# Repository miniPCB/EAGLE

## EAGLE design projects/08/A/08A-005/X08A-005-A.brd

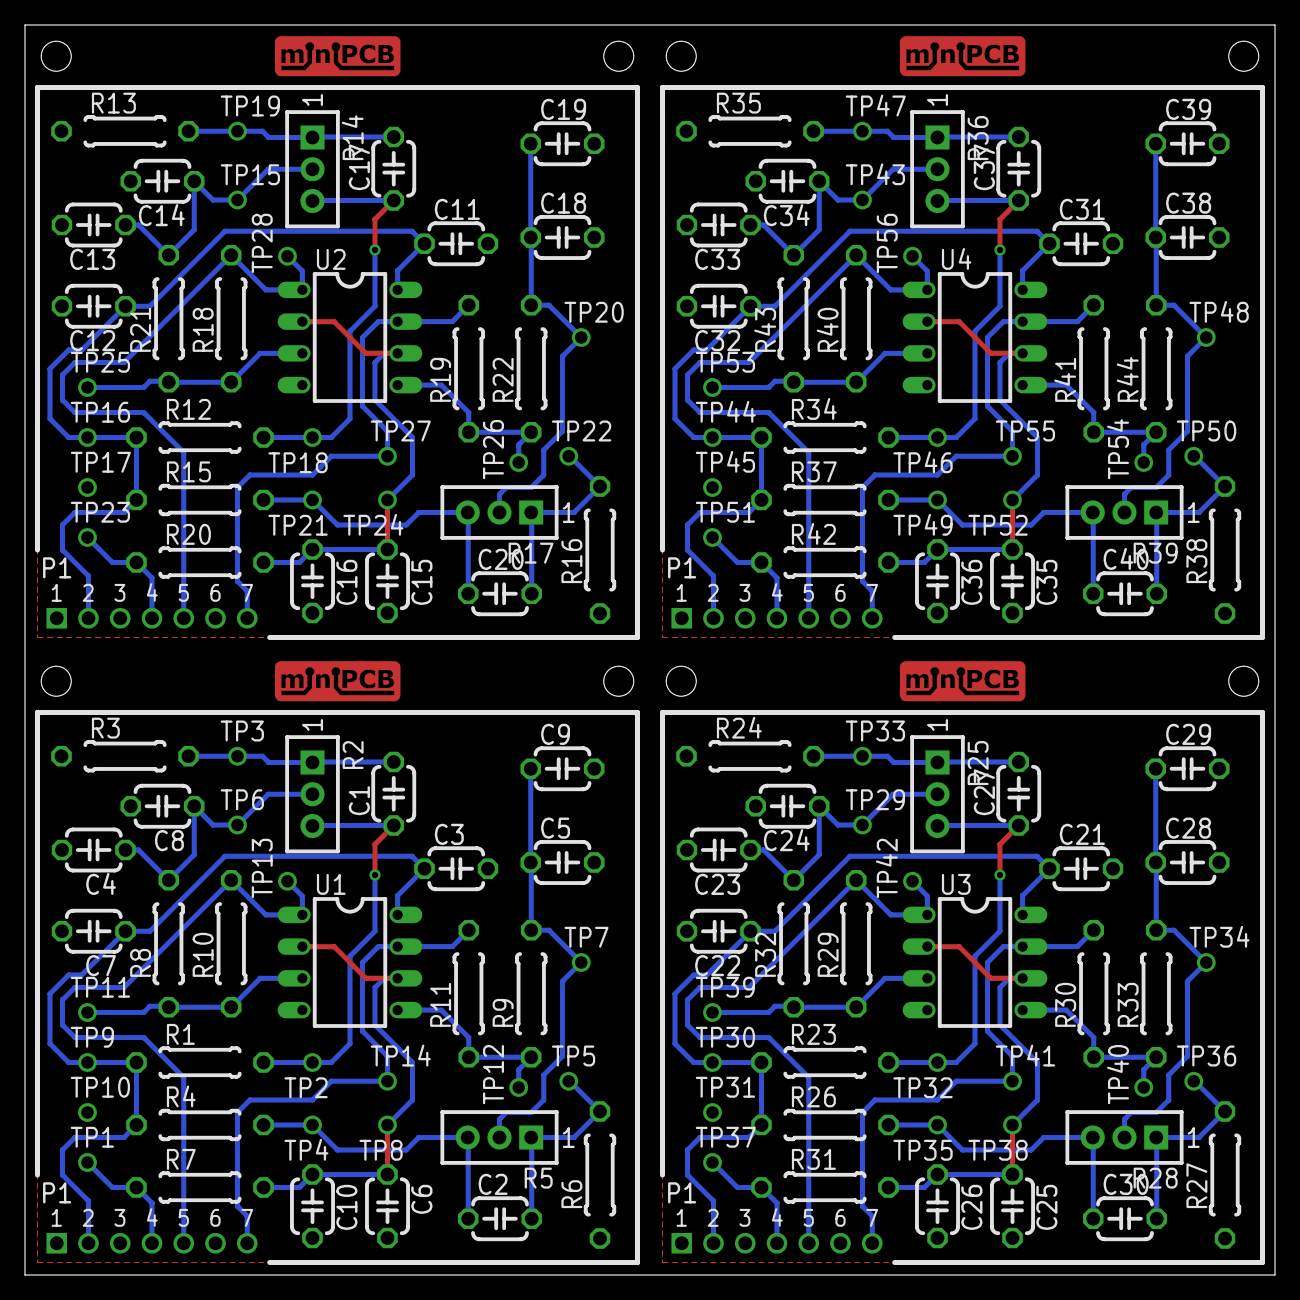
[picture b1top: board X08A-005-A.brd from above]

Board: 2 copper layers, 100.0 x 100.0 mm, 149 parts (0 on the bottom side), 56 nets.

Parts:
C1, C2, C3, C4, C5, C6, C7, C8, C9, C10, C11, C12, C13, C14, C15, C16, C17, C18, C19, C20, C21, C22, C23, C24, C25, C26, C27, C28, C29, C30, C31, C32, C33, C34, C35, C36, C37, C38, C39, C40: C050-024X044
E$1: MINIPCB_PANEL_IMAGEFRAME
P1-, P1-1, P1-2, P1-3: MINIPCB_7P_50X50
R1, R3, R4, R6, R7, R8, R9, R10, R11, R12, R13, R15, R16, R18, R19, R20, R21, R22, R23, R24, R26, R27, R29, R30, R31, R32, R33, R34, R35, R37, R38, R40, R41, R42, R43, R44: 0207/10
R2, R5, R14, R17, R25, R28, R36, R39: TRIM_0100
TP1, TP2, TP3, TP4, TP5, TP6, TP7, TP8, TP9, TP10, TP11, TP12, TP13, TP14, TP15, TP16, TP17, TP18, TP19, TP20, TP21, TP22, TP23, TP24, TP25, TP26, TP27, TP28, TP29, TP30, TP31, TP32, TP33, TP34, TP35, TP36, TP37, TP38, TP39, TP40, TP41, TP42, TP43, TP44, TP45, TP46, TP47, TP48, TP49, TP50, TP51, TP52, TP53, TP54, TP55, TP56: PINS_1_TESTPOINT_KE5000_NOTEXT
U1, U2, U3, U4: DIL08

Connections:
BIASA: C4.1, C8.1, R2.2, R8.2, TP6.1
BIASA1: C13.1, C14.1, R14.2, R21.2, TP15.1
BIASA2: C23.1, C24.1, R25.2, R32.2, TP29.1
BIASA3: C33.1, C34.1, R36.2, R43.2, TP43.1
BIASB: C5.1, C9.1, R5.2, R9.2, TP7.1
BIASB1: C18.1, C19.1, R17.2, R22.2, TP20.1
BIASB2: C28.1, C29.1, R28.2, R33.2, TP34.1
BIASB3: C38.1, C39.1, R39.2, R44.2, TP48.1
GND: C3.2, C4.2, C5.2, C6.2, C7.2, C8.2, C9.2, C10.2, P1-.1, R3.1, R6.1, TP10.1, U1.4
GND1: C11.2, C12.2, C13.2, C14.2, C15.2, C16.2, C18.2, C19.2, P1-1.1, R13.1, R16.1, TP17.1, U2.4
GND2: C21.2, C22.2, C23.2, C24.2, C25.2, C26.2, C28.2, C29.2, P1-2.1, R24.1, R27.1, TP31.1, U3.4
GND3: C31.2, C32.2, C33.2, C34.2, C35.2, C36.2, C38.2, C39.2, P1-3.1, R35.1, R38.1, TP45.1, U4.4
IN: P1-.4, R7.1, TP1.1
IN1: P1-1.4, R20.1, TP23.1
IN2: P1-2.4, R31.1, TP37.1
IN3: P1-3.4, R42.1, TP51.1
IN-4: C6.1, C10.1, R7.2, TP8.1, U1.2, U1.6
IN-5: C15.1, C16.1, R20.2, TP24.1, U2.2, U2.6
IN-6: C25.1, C26.1, R31.2, TP38.1, U3.2, U3.6
IN-7: C35.1, C36.1, R42.2, TP52.1, U4.2, U4.6
INA+: R8.1, R10.1, TP11.1, U1.3
INA+1: R18.1, R21.1, TP25.1, U2.3
INA+2: R29.1, R32.1, TP39.1, U3.3
INA+3: R40.1, R43.1, TP53.1, U4.3
INB+: R9.1, R11.1, TP12.1, U1.5
INB+1: R19.1, R22.1, TP26.1, U2.5
INB+2: R30.1, R33.1, TP40.1, U3.5
INB+3: R41.1, R44.1, TP54.1, U4.5
OUTA: P1-.5, R10.2, TP13.1, U1.1
OUTA1: P1-1.5, R18.2, TP28.1, U2.1
OUTA2: P1-2.5, R29.2, TP42.1, U3.1
OUTA3: P1-3.5, R40.2, TP56.1, U4.1
OUTB: P1-.7, R11.2, TP14.1, U1.7
OUTB1: P1-1.7, R19.2, TP27.1, U2.7
OUTB2: P1-2.7, R30.2, TP41.1, U3.7
OUTB3: P1-3.7, R41.2, TP55.1, U4.7
R2.1: C1.1, R1.2, R2.3, TP2.1
R2.4: C1.2, R2.1, R3.2, TP3.1
R2.6: C17.1, R12.2, R14.3, TP18.1
R2.8: C17.2, R13.2, R14.1, TP19.1
R2.9: C27.1, R23.2, R25.3, TP32.1
R2.10: C27.2, R24.2, R25.1, TP33.1
R2.11: C37.1, R34.2, R36.3, TP46.1
R2.12: C37.2, R35.2, R36.1, TP47.1
R5.1: C2.2, R5.1, R6.2, TP5.1
R5.2: C20.1, R15.2, R17.3, TP21.1
R5.3: C2.1, R4.2, R5.3, TP4.1
R5.4: C20.2, R16.2, R17.1, TP22.1
R5.5: C30.1, R26.2, R28.3, TP35.1
R5.6: C30.2, R27.2, R28.1, TP36.1
R5.7: C40.1, R37.2, R39.3, TP49.1
R5.8: C40.2, R38.2, R39.1, TP50.1
V+: C3.1, C7.1, P1-.2, R1.1, R4.1, TP9.1, U1.8
V+1: C11.1, C12.1, P1-1.2, R12.1, R15.1, TP16.1, U2.8
V+2: C21.1, C22.1, P1-2.2, R23.1, R26.1, TP30.1, U3.8
V+3: C31.1, C32.1, P1-3.2, R34.1, R37.1, TP44.1, U4.8

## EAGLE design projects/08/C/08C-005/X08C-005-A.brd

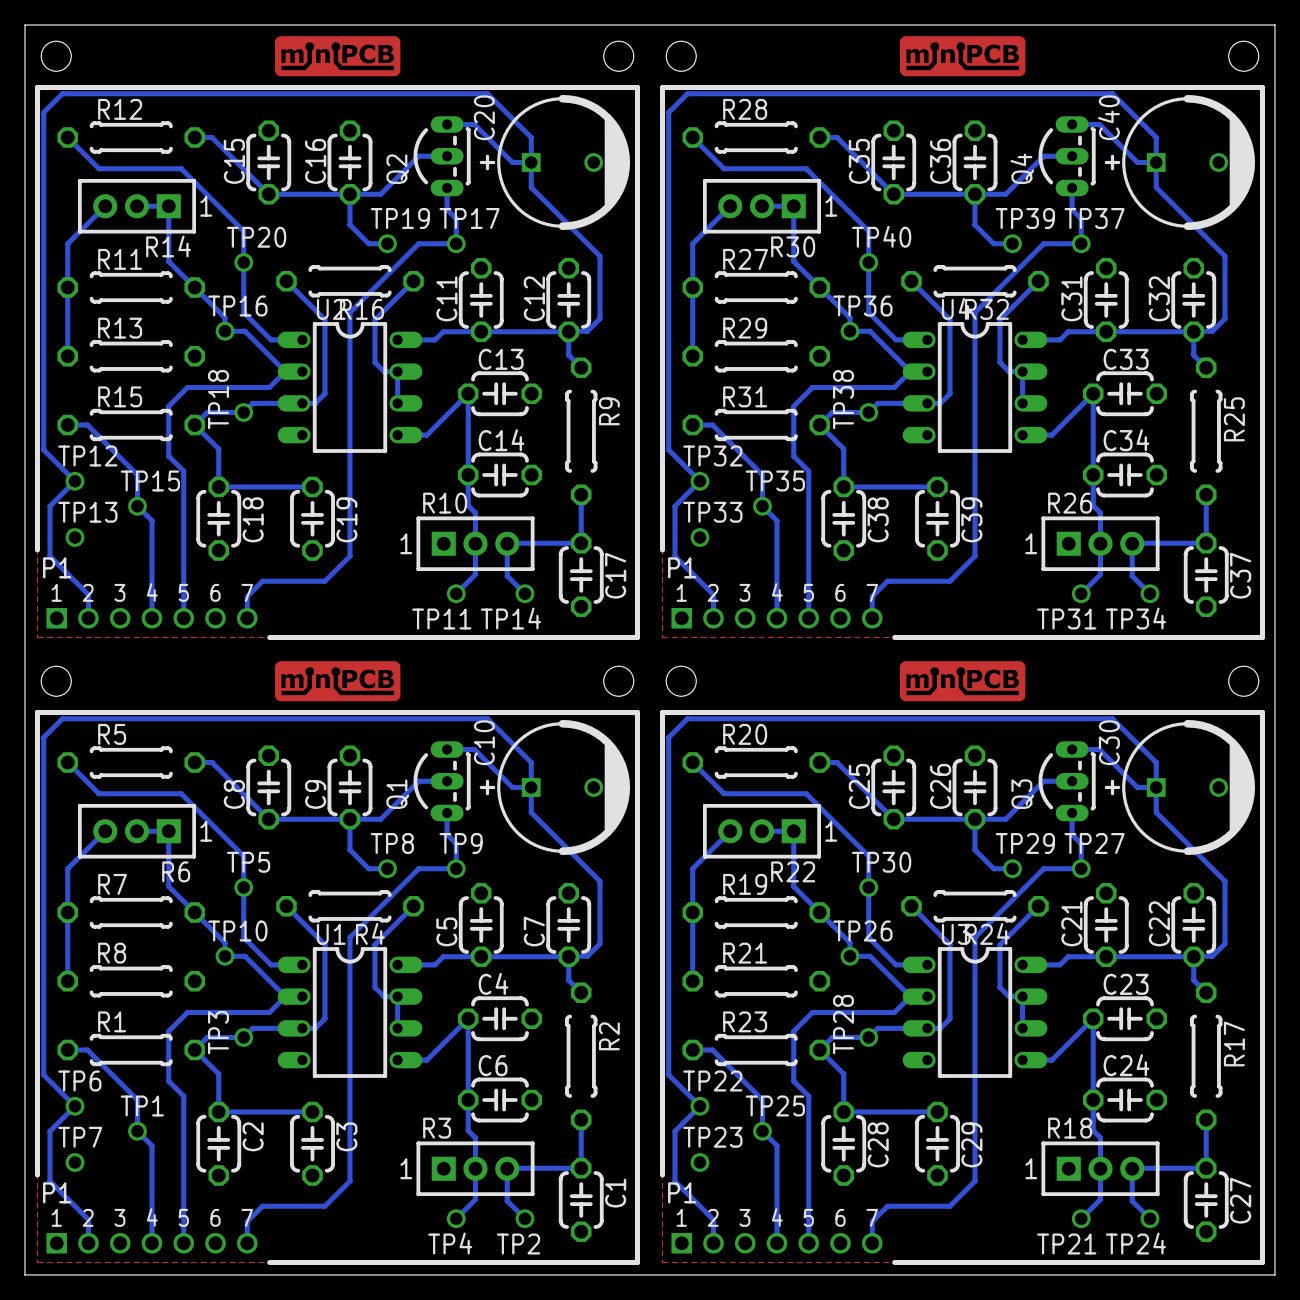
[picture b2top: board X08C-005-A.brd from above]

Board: 2 copper layers, 100.0 x 100.0 mm, 125 parts (0 on the bottom side), 48 nets.

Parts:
C1, C2, C3, C4, C5, C6, C7, C8, C9, C11, C12, C13, C14, C15, C16, C17, C18, C19, C21, C22, C23, C24, C25, C26, C27, C28, C29, C31, C32, C33, C34, C35, C36, C37, C38, C39: C050-024X044
C10, C20, C30, C40: C5MM
E$1: MINIPCB_PANEL_IMAGEFRAME
P1-, P1-1, P1-2, P1-3: MINIPCB_7P_50X50
Q1, Q2, Q3, Q4: TO92-EBC-OVAL
R1, R2, R4, R5, R7, R8, R9, R11, R12, R13, R15, R16, R17, R19, R20, R21, R23, R24, R25, R27, R28, R29, R31, R32: 0207/10
R3, R6, R10, R14, R18, R22, R26, R30: TRIM_0100
TP1, TP2, TP3, TP4, TP5, TP6, TP7, TP8, TP9, TP10, TP11, TP12, TP13, TP14, TP15, TP16, TP17, TP18, TP19, TP20, TP21, TP22, TP23, TP24, TP25, TP26, TP27, TP28, TP29, TP30, TP31, TP32, TP33, TP34, TP35, TP36, TP37, TP38, TP39, TP40: PINS_1_TESTPOINT_KE5000_NOTEXT
U1, U2, U3, U4: DIL08

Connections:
BIAS: C4.1, C6.1, R3.2, TP4.1, U1.5
BIAS1: C13.1, C14.1, R10.2, TP11.1, U2.5
BIAS2: C23.1, C24.1, R18.2, TP21.1, U3.5
BIAS3: C33.1, C34.1, R26.2, TP31.1, U4.5
GND: C1.2, C2.2, C3.2, C4.2, C5.2, C6.2, C7.2, C8.2, C9.2, C10.-, P1-.1, P1-.6, R3.1, R8.2, TP7.1, U1.4
GND1: C11.2, C12.2, C13.2, C14.2, C15.2, C16.2, C17.2, C18.2, C19.2, C20.-, P1-1.1, P1-1.6, R10.1, R13.2, TP13.1, U2.4
GND2: C21.2, C22.2, C23.2, C24.2, C25.2, C26.2, C27.2, C28.2, C29.2, C30.-, P1-2.1, P1-2.6, R18.1, R21.2, TP23.1, U3.4
GND3: C31.2, C32.2, C33.2, C34.2, C35.2, C36.2, C37.2, C38.2, C39.2, C40.-, P1-3.1, P1-3.6, R26.1, R29.2, TP33.1, U4.4
IN: R4.1, U1.6, U1.7
IN1: R16.1, U2.6, U2.7
IN2: R24.1, U3.6, U3.7
IN3: R32.1, U4.6, U4.7
unnamed: C2.1, C3.1, R1.2, R4.2, TP3.1, U1.3
unnamed: P1-.4, R1.1, TP1.1
unnamed: P1-1.4, R15.1, TP15.1
unnamed: C18.1, C19.1, R15.2, R16.2, TP18.1, U2.3
unnamed: P1-2.4, R23.1, TP25.1
unnamed: C28.1, C29.1, R23.2, R24.2, TP28.1, U3.3
unnamed: P1-3.4, R31.1, TP35.1
unnamed: C38.1, C39.1, R31.2, R32.2, TP38.1, U4.3
OUT+: P1-.7, Q1.E, TP9.1
OUT+1: P1-1.7, Q2.E, TP17.1
OUT+2: P1-2.7, Q3.E, TP27.1
OUT+3: P1-3.7, Q4.E, TP37.1
OUT-: P1-.5, R6.1, R6.2, R7.2, TP10.1, U1.2
OUT-1: P1-1.5, R11.2, R14.1, R14.2, TP16.1, U2.2
OUT-2: P1-2.5, R19.2, R22.1, R22.2, TP26.1, U3.2
OUT-3: P1-3.5, R27.2, R30.1, R30.2, TP36.1, U4.2
Q1.B: C8.1, C9.1, Q1.B, R5.2, TP8.1
Q1.B1: C15.1, C16.1, Q2.B, R12.2, TP19.1
Q1.B2: C25.1, C26.1, Q3.B, R20.2, TP29.1
Q1.B3: C35.1, C36.1, Q4.B, R28.2, TP39.1
R2.1: C17.1, R9.2, R10.3, TP14.1
R2.2: C27.1, R17.2, R18.3, TP24.1
R2.3: C1.1, R2.2, R3.3, TP2.1
R2.4: C37.1, R25.2, R26.3, TP34.1
R6.1: R11.1, R13.1, R14.3
R6.2: R19.1, R21.1, R22.3
R6.3: R6.3, R7.1, R8.1
R6.4: R27.1, R29.1, R30.3
U1.1: R5.1, TP5.1, U1.1
U1.2: R12.1, TP20.1, U2.1
U1.3: R20.1, TP30.1, U3.1
U1.4: R28.1, TP40.1, U4.1
V+: C5.1, C7.1, C10.+, P1-.2, Q1.C, R2.1, TP6.1, U1.8
V+1: C11.1, C12.1, C20.+, P1-1.2, Q2.C, R9.1, TP12.1, U2.8
V+2: C21.1, C22.1, C30.+, P1-2.2, Q3.C, R17.1, TP22.1, U3.8
V+3: C31.1, C32.1, C40.+, P1-3.2, Q4.C, R25.1, TP32.1, U4.8

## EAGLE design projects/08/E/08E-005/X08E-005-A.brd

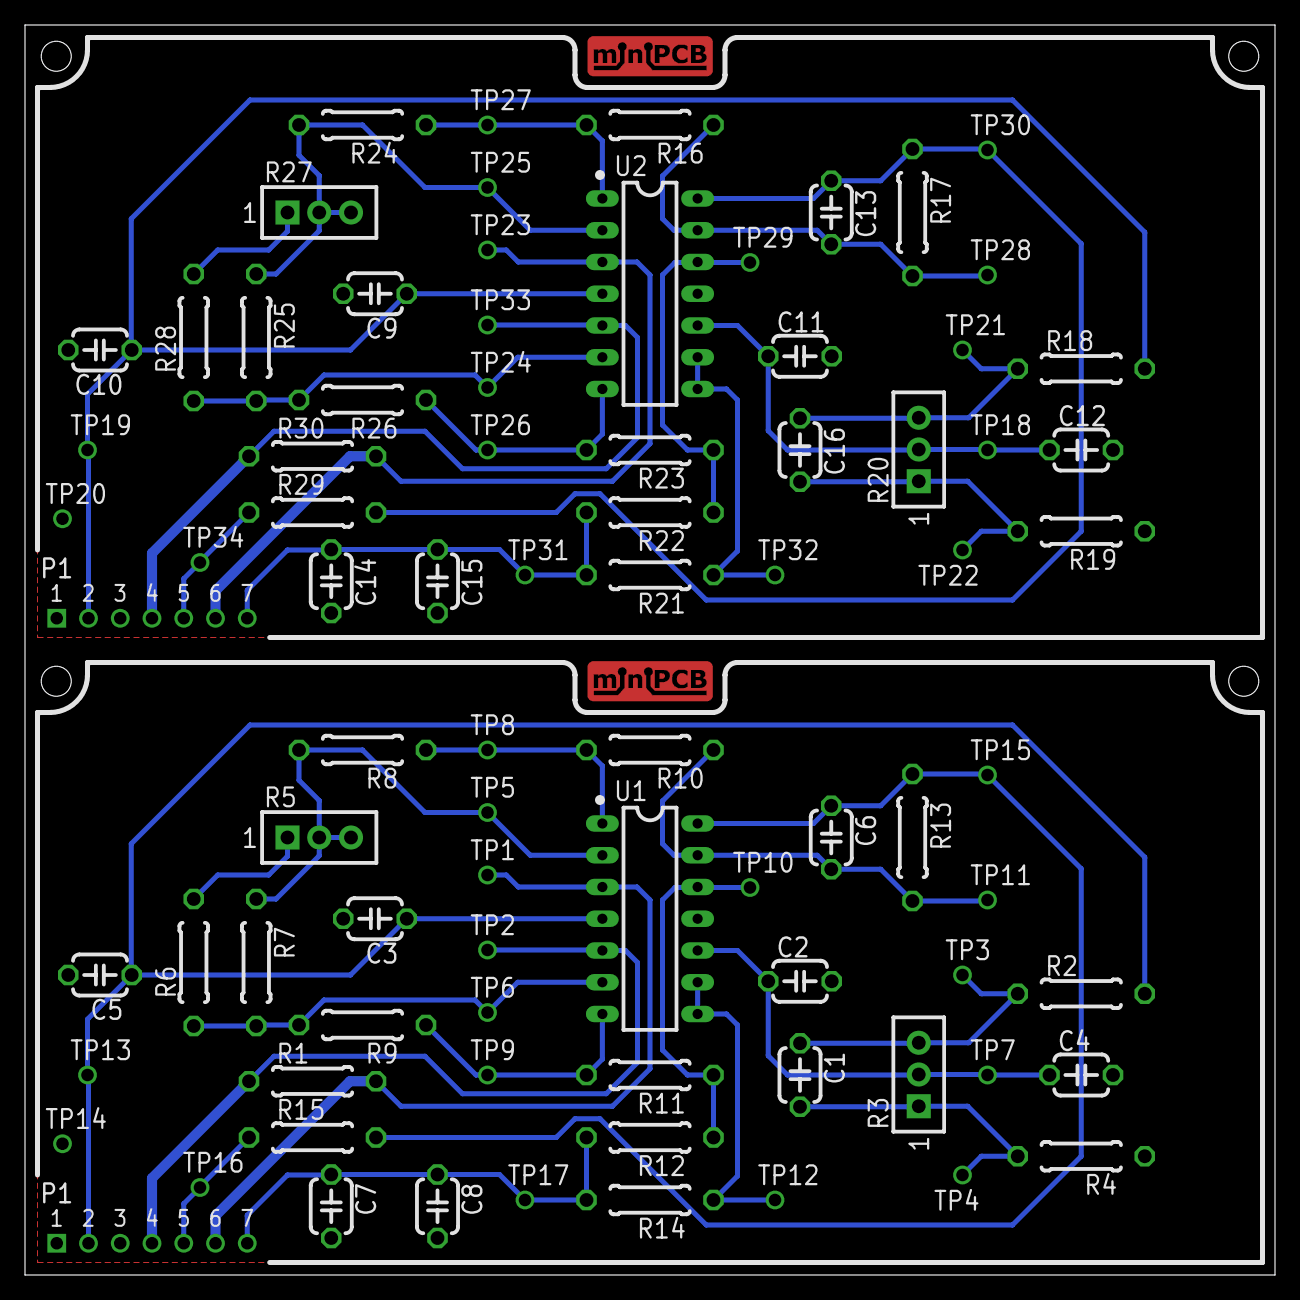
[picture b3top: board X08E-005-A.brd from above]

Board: 2 copper layers, 100.0 x 100.0 mm, 85 parts (0 on the bottom side), 36 nets.

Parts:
C1, C2, C3, C4, C5, C6, C7, C8, C9, C10, C11, C12, C13, C14, C15, C16: C050-024X044
E$1: MINIPCB_PANEL_IMAGEFRAME
P1-, P1-1: MINIPCB_7P_50X100
R1, R2, R4, R6, R7, R8, R9, R10, R11, R12, R13, R14, R15, R16, R17, R18, R19, R21, R22, R23, R24, R25, R26, R28, R29, R30: 0207/10
R3, R5, R20, R27: TRIM_0100
TP1, TP2, TP3, TP4, TP5, TP6, TP7, TP8, TP9, TP10, TP11, TP12, TP13, TP14, TP15, TP16, TP17, TP18, TP19, TP20, TP21, TP22, TP23, TP24, TP25, TP26, TP27, TP28, TP29, TP30, TP31, TP32, TP33, TP34: PINS_1_TESTPOINT_KE5000_NOTEXT
U1, U2: DIL14

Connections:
BIAS: C2.1, C4.1, R3.2, TP7.1, U1.10
BIAS1: C11.1, C12.1, R20.2, TP18.1, U2.10
GND: C2.2, C3.2, C4.2, C5.2, C7.2, C8.2, P1-.1, R4.1, TP14.1, U1.11
GND1: C9.2, C10.2, C11.2, C12.2, C14.2, C15.2, P1-1.1, R19.1, TP20.1, U2.11
unnamed: R11.1, R12.1, TP10.1, U1.12
unnamed: C7.1, C8.1, P1-.7, R12.2, R14.2, TP17.1
unnamed: P1-.4, R1.1, TP2.1, U1.5
unnamed: P1-.6, R1.2, TP1.1, U1.3
unnamed: R5.2, R5.3, R7.1, R8.2, TP5.1, U1.2
unnamed: R6.1, R7.2, R9.2, TP6.1, U1.6
unnamed: R8.1, R10.2, TP8.1, U1.1
unnamed: R9.1, R11.2, TP9.1, U1.7
unnamed: R14.1, TP12.1, U1.8, U1.9
unnamed: R5.1, R6.2
unnamed: P1-.5, R15.1, TP16.1
unnamed: R22.1, R23.1, TP29.1, U2.12
unnamed: C14.1, C15.1, P1-1.7, R21.2, R22.2, TP31.1
unnamed: P1-1.4, R30.1, TP33.1, U2.5
unnamed: P1-1.6, R30.2, TP23.1, U2.3
unnamed: R24.2, R25.1, R27.2, R27.3, TP25.1, U2.2
unnamed: R25.2, R26.2, R28.1, TP24.1, U2.6
unnamed: R16.2, R24.1, TP27.1, U2.1
unnamed: R23.2, R26.1, TP26.1, U2.7
unnamed: R21.1, TP32.1, U2.8, U2.9
unnamed: R27.1, R28.2
unnamed: P1-1.5, R29.1, TP34.1
OUT: C6.1, R13.1, R15.2, TP15.1, U1.14
OUT1: C13.1, R17.1, R29.2, TP30.1, U2.14
POT.1: C1.2, R3.1, R4.2, TP4.1
POT.2: C16.1, R18.1, R20.3, TP21.1
POT.3: C1.1, R2.1, R3.3, TP3.1
POT.4: C16.2, R19.2, R20.1, TP22.1
V+: C3.1, C5.1, P1-.2, R2.2, TP13.1, U1.4
V+1: C9.1, C10.1, P1-1.2, R18.2, TP19.1, U2.4
VFB: C6.2, R10.1, R13.2, TP11.1, U1.13
VFB1: C13.2, R16.1, R17.2, TP28.1, U2.13
